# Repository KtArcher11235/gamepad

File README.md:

# gamepad
a fun macropad for gaming

## Bom:
- 1 unsoldered Seeed XIAO RP2040
- 20x through-hole 1N4148 Diodes
- 16(+4)x MX-Style switches
- 16(+4)x white blank DSA keycaps
- 20x SK6812 MINI-E LEDs
- 4x M3x16mm screws
- 4x M3x5mx4mm heatset inserts

## take a look
https://kicanvas.org/?repo=https%3A%2F%2Fgithub.com%2FKtArcher11235%2Fgamepad%2Ftree%2Fmain%2FPCB

https://github.com/user-attachments/assets/3bd6342f-658d-492e-aa05-4c56db0929b1

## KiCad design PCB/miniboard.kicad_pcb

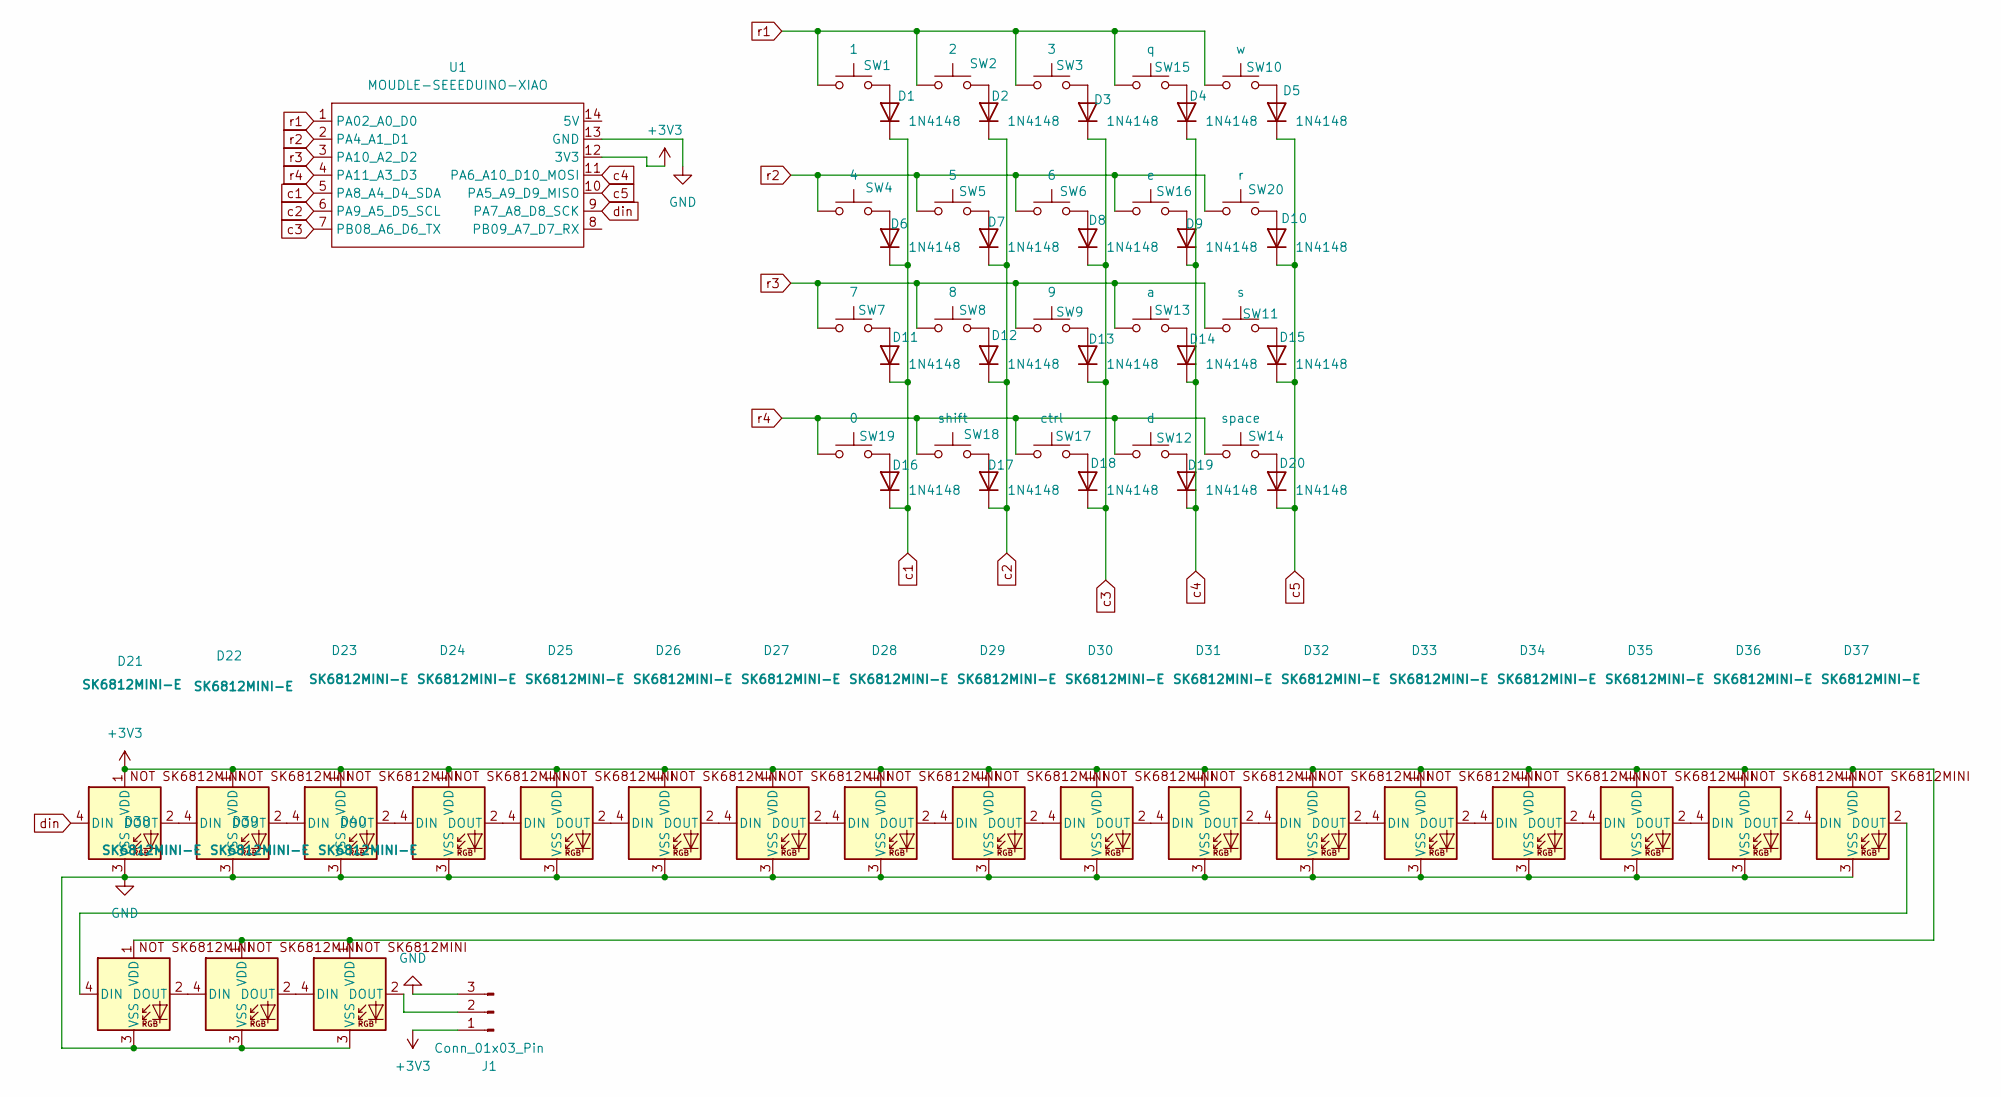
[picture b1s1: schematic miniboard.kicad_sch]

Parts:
D1, D2, D3, D4, D5, D6, D7, D8, D9, D10, D11, D12, D13, D14, D15, D16, D17, D18, D19, D20: 1N4148; D_DO-35_SOD27_P7.62mm_Horizontal
D21, D22, D23, D24, D25, D26, D27, D28, D29, D30, D31, D32, D33, D34, D35, D36, D37, D38, D39, D40: SK6812MINI-E; SK6812MINI-E_fixed
J1: Conn_01x03_Pin; PinHeader_1x03_P2.54mm_Vertical
SW1: 1; SW_Cherry_MX_1.00u_PCB3d
SW2: 2; SW_Cherry_MX_1.00u_PCB3d
SW3: 3; SW_Cherry_MX_1.00u_PCB3d
SW4: 4; SW_Cherry_MX_1.00u_PCB3d
SW5: 5; SW_Cherry_MX_1.00u_PCB3d
SW6: 6; SW_Cherry_MX_1.00u_PCB3d
SW7: 7; SW_Cherry_MX_1.00u_PCB3d
SW8: 8; SW_Cherry_MX_1.00u_PCB3d
SW9: 9; SW_Cherry_MX_1.00u_PCB3d
SW10: w; SW_Cherry_MX_1.00u_PCB3d
SW11: s; SW_Cherry_MX_1.00u_PCB3d
SW12: d; SW_Cherry_MX_1.00u_PCB3d
SW13: a; SW_Cherry_MX_1.00u_PCB3d
SW14: space; SW_Cherry_MX_1.00u_PCB3d
SW15: q; SW_Cherry_MX_1.00u_PCB3d
SW16: e; SW_Cherry_MX_1.00u_PCB3d
SW17: ctrl; SW_Cherry_MX_1.00u_PCB3d
SW18: shift; SW_Cherry_MX_1.00u_PCB3d
SW19: 0; SW_Cherry_MX_1.00u_PCB3d
SW20: r; SW_Cherry_MX_1.00u_PCB3d
U1: MOUDLE-SEEEDUINO-XIAO; XIAO-Generic-Hybrid-14P-2.54-21X17.8MM

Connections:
+3V3: D21.1 (VDD), D22.1 (VDD), D23.1 (VDD), D24.1 (VDD), D25.1 (VDD), D26.1 (VDD), D27.1 (VDD), D28.1 (VDD), D29.1 (VDD), D30.1 (VDD), D31.1 (VDD), D32.1 (VDD), D33.1 (VDD), D34.1 (VDD), D35.1 (VDD), D36.1 (VDD), D37.1 (VDD), D38.1 (VDD), D39.1 (VDD), D40.1 (VDD), J1.1, U1.12 (3V3)
GND: D21.3 (VSS), D22.3 (VSS), D23.3 (VSS), D24.3 (VSS), D25.3 (VSS), D26.3 (VSS), D27.3 (VSS), D28.3 (VSS), D29.3 (VSS), D30.3 (VSS), D31.3 (VSS), D32.3 (VSS), D33.3 (VSS), D34.3 (VSS), D35.3 (VSS), D36.3 (VSS), D37.3 (VSS), D38.3 (VSS), D39.3 (VSS), D40.3 (VSS), J1.3, U1.13 (GND)
unnamed: D1.2 (A), SW1.2
unnamed: D2.2 (A), SW2.2
unnamed: D3.2 (A), SW3.2
unnamed: D4.2 (A), SW15.2
unnamed: D5.2 (A), SW10.2
unnamed: D6.2 (A), SW4.2
unnamed: D7.2 (A), SW5.2
unnamed: D8.2 (A), SW6.2
unnamed: D9.2 (A), SW16.2
unnamed: D10.2 (A), SW20.2
unnamed: D11.2 (A), SW7.2
unnamed: D12.2 (A), SW8.2
unnamed: D13.2 (A), SW9.2
unnamed: D14.2 (A), SW13.2
unnamed: D15.2 (A), SW11.2
unnamed: D16.2 (A), SW19.2
unnamed: D17.2 (A), SW18.2
unnamed: D18.2 (A), SW17.2
unnamed: D19.2 (A), SW12.2
unnamed: D20.2 (A), SW14.2
unnamed: D21.2 (DOUT), D22.4 (DIN)
unnamed: D22.2 (DOUT), D23.4 (DIN)
unnamed: D23.2 (DOUT), D24.4 (DIN)
unnamed: D24.2 (DOUT), D25.4 (DIN)
unnamed: D25.2 (DOUT), D26.4 (DIN)
unnamed: D26.2 (DOUT), D27.4 (DIN)
unnamed: D27.2 (DOUT), D28.4 (DIN)
unnamed: D28.2 (DOUT), D29.4 (DIN)
unnamed: D29.2 (DOUT), D30.4 (DIN)
unnamed: D30.2 (DOUT), D31.4 (DIN)
unnamed: D31.2 (DOUT), D32.4 (DIN)
unnamed: D32.2 (DOUT), D33.4 (DIN)
unnamed: D33.2 (DOUT), D34.4 (DIN)
unnamed: D34.2 (DOUT), D35.4 (DIN)
unnamed: D35.2 (DOUT), D36.4 (DIN)
unnamed: D36.2 (DOUT), D37.4 (DIN)
unnamed: D37.2 (DOUT), D38.4 (DIN)
unnamed: D38.2 (DOUT), D39.4 (DIN)
unnamed: D39.2 (DOUT), D40.4 (DIN)
unnamed: D40.2 (DOUT), J1.2
c1: D1.1 (K), D6.1 (K), D11.1 (K), D16.1 (K), U1.5 (PA8_A4_D4_SDA)
c2: D2.1 (K), D7.1 (K), D12.1 (K), D17.1 (K), U1.6 (PA9_A5_D5_SCL)
c3: D3.1 (K), D8.1 (K), D13.1 (K), D18.1 (K), U1.7 (PB08_A6_D6_TX)
c4: D4.1 (K), D9.1 (K), D14.1 (K), D19.1 (K), U1.11 (PA6_A10_D10_MOSI)
c5: D5.1 (K), D10.1 (K), D15.1 (K), D20.1 (K), U1.10 (PA5_A9_D9_MISO)
din: D21.4 (DIN), U1.9 (PA7_A8_D8_SCK)
r1: SW1.1, SW2.1, SW3.1, SW10.1, SW15.1, U1.1 (PA02_A0_D0)
r2: SW4.1, SW5.1, SW6.1, SW16.1, SW20.1, U1.2 (PA4_A1_D1)
r3: SW7.1, SW8.1, SW9.1, SW11.1, SW13.1, U1.3 (PA10_A2_D2)
r4: SW12.1, SW14.1, SW17.1, SW18.1, SW19.1, U1.4 (PA11_A3_D3)

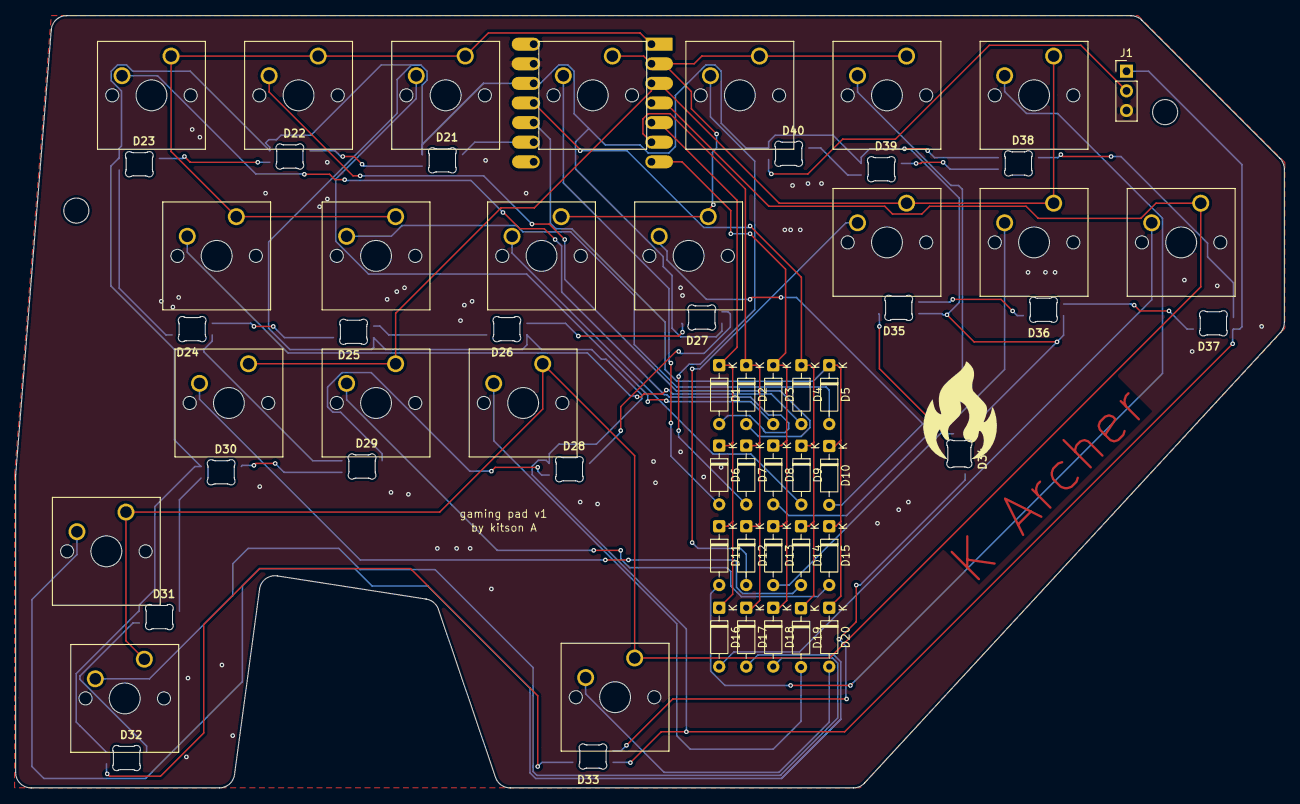
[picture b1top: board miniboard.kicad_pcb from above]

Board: 2 copper layers, 164.3 x 100.0 mm, 62 parts (1 on the bottom side), 52 nets.

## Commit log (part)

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2026-06-13 Add image to README for visual enhancement
    Added an image to the README for better visual representation.
2026-06-14 Add CAD STEP and KiCad miniboard files
    Add 3D CAD model and KiCad project for the miniboard: Cad/cad.step (AP242 STEP export), and PCB/miniboard.{kicad_pcb,kicad_pro,kicad_sch}. Provides the 3D model plus schematic and PCB layout for deve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
2026-06-14 Add production Gerbers and STEP files
    Add Production/Gerbers.zip plus 3D CAD exports Production/top.step and Production/bottom.step.
2026-06-14 Update README with images and BOM information
    Added images and BOM details for the macropad project.
2026-06-14 Fix BOM formatting in README.md
2026-06-24 Add special notes for hc people in README
    Added special notes for hc people regarding PCB size and key switches.
